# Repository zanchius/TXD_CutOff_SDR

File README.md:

# TXD_CutOff_SDR
A FET/Relay based RF/TXD cutoff switch to protect SDR receivers which share the same antenna with a transceiver.
Input signal from the transceiver, in this case a Yaesu FT-991A is taken from the SQL pin on the Data port miniDIN 6 pins socket, as it's on a HIGH 5V level during RX and LOW 0V on TX.
The relay is constantly energised with the HIGH signal and will disconnect the SDR under a LOW signal.

Partlist in the repository

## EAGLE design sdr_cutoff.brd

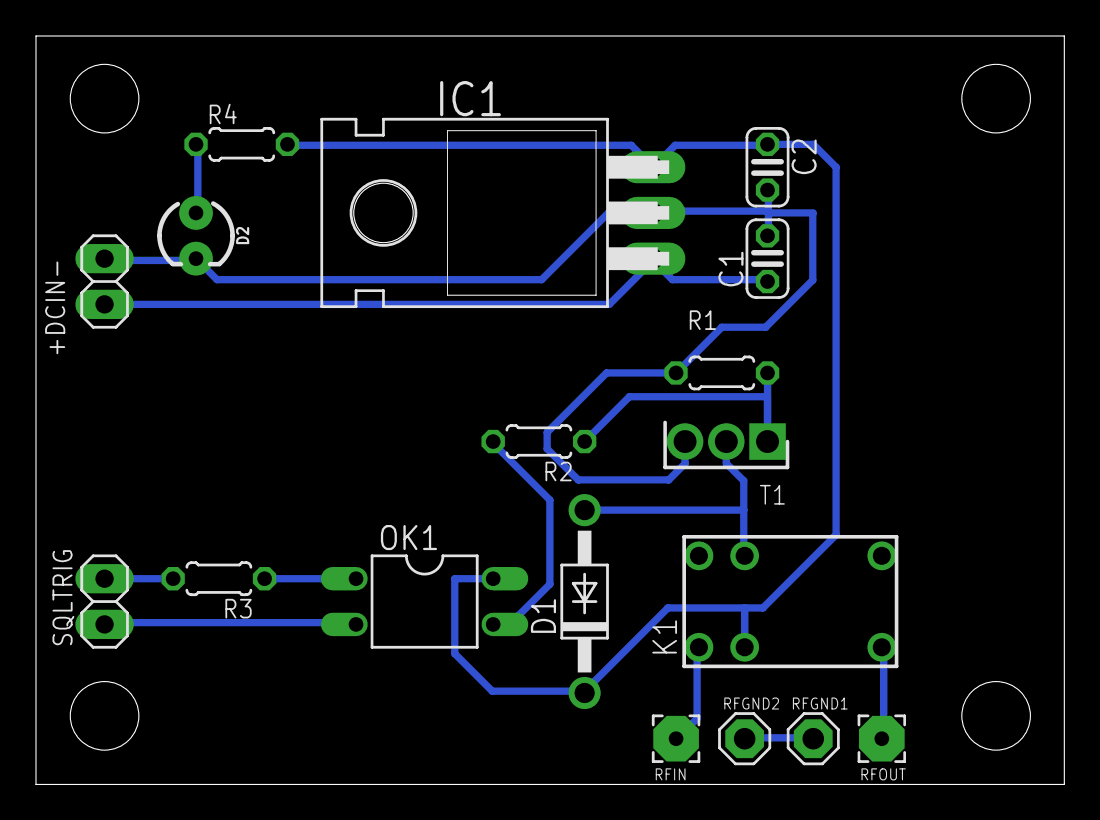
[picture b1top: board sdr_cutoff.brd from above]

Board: 2 copper layers, 57.1 x 41.6 mm, 18 parts (0 on the bottom side), 13 nets.

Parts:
+DCIN-: 1X02
C1: 0.22uF; C025-024X044
C2: 0.10uF; C025-024X044
D1: 1N4004; DO41-10
D2: LED_3MM
IC1: 7805T; TO220H
K1: HY1Z-5V; HY
OK1: PC814; DIL04
R1: 100K; 0204/5
R2, R3, R4: 1K; 0204/5
RFGND1, RFGND2: MCS08
RFIN: 2,54/0,8
RFOUT: 2,54/0,8
SQLTRIG: 1X02
T1: RFD14N05L; TO229P250X658X985-3P

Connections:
GND: +DCIN-.1, C1.2, C2.2, D2.K, IC1.2, R1.1, T1.3
unnamed: D1.A, K1.2, T1.2
unnamed: OK1.3, R2.2
unnamed: R1.2, R2.1, T1.1
unnamed: OK1.1, R3.1
unnamed: OK1.2, SQLTRIG.1
unnamed: R3.2, SQLTRIG.2
unnamed: RFGND1.MP, RFGND2.MP
unnamed: +DCIN-.2, C1.1, IC1.1
unnamed: K1.NC, RFIN.1
unnamed: D2.A, R4.1
unnamed: K1.C@2, RFOUT.1
VCC: C2.1, D1.C, IC1.3, K1.1, OK1.4, R4.2

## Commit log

2022-01-29 Add files via upload
    Corrected missing ground on DC block
2022-02-13 Add files via upload
    Corrected minor errors and finalised PCB layout
2022-02-13 Rename SDR_Cutoff to SDR_Cutoff_BOM.txt

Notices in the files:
parts and their libraries:
SparkFun-LED: Licensing: Creative Commons ShareAlike 4.0 International - https://creativecommons.org/licenses/by-sa/4.0
